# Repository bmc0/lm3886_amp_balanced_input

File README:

A 50W@8Ω balanced-input power amp using the LM3886 chip.

Directories:
  lm3886_amp_balanced_input/    - Amplifier board (one channel)
  lm3886_psu/                   - Power supply (2-channel version)
  lm3886_psu_4ch/               - Power supply (4-channel version)
  lm3886_soft_start_v2/         - Optional soft start

License:
  All works contained in this repository are released under a
  CC BY-SA 4.0 license. Copyright (c) Michael Barbour, 2020.

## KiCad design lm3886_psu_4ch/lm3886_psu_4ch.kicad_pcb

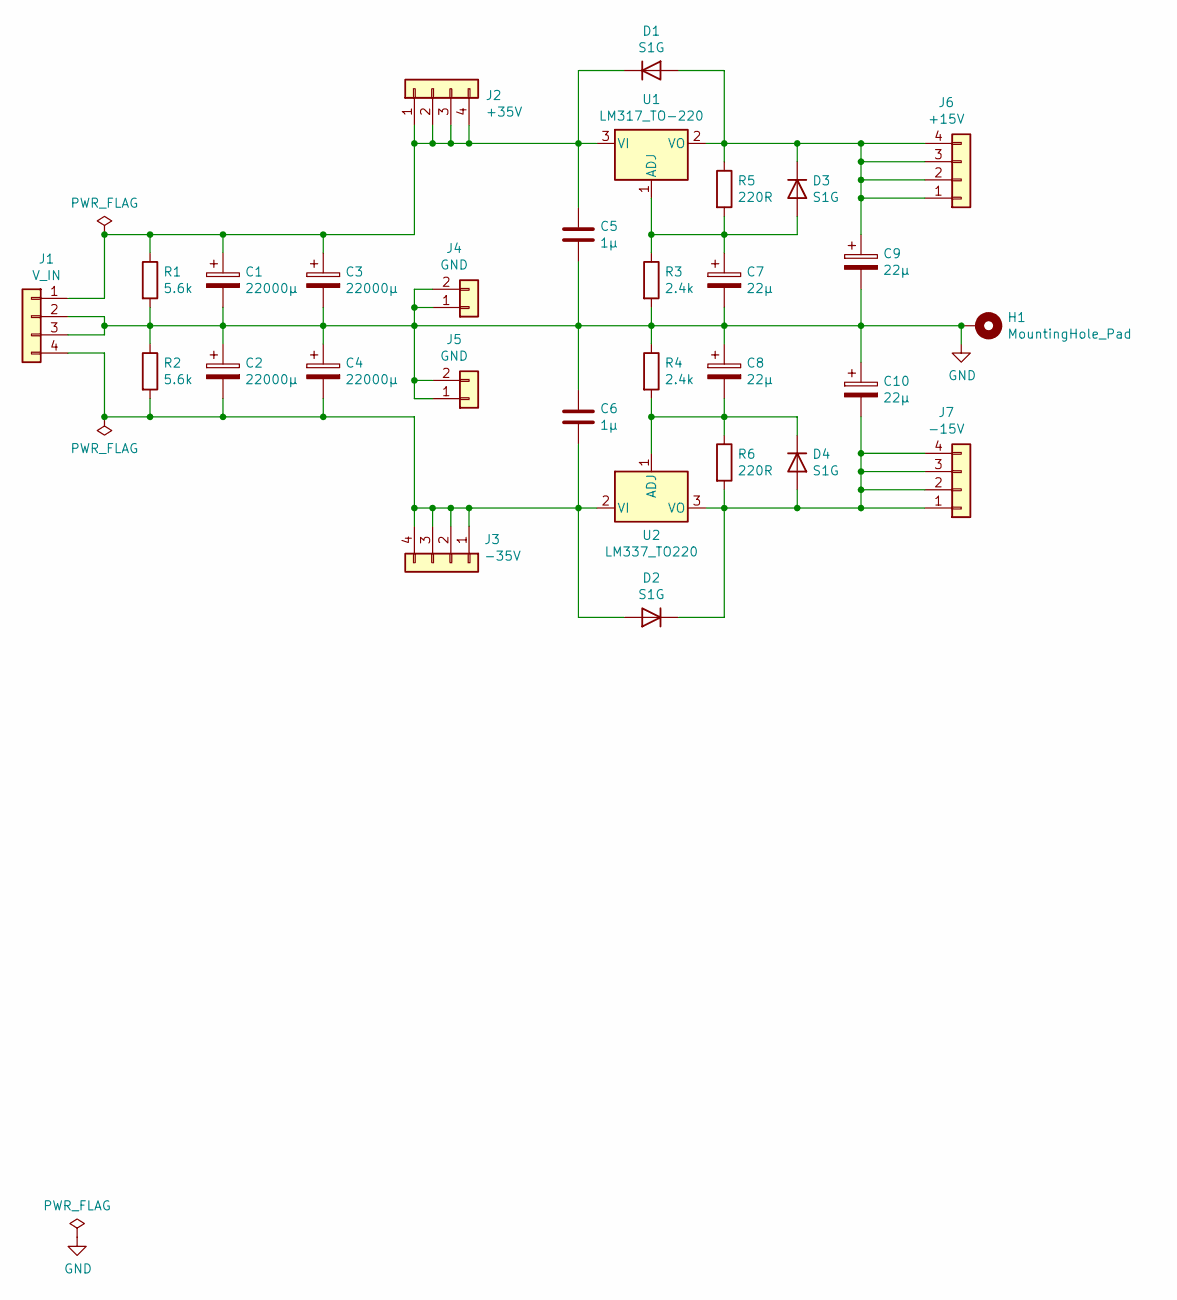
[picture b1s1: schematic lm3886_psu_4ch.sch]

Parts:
C1, C2, C3, C4: 22000µ; CP_Radial_D35.0mm_P10.00mm_SnapIn
C5, C6: 1µ; C_1206_3216Metric
C7, C8, C9, C10: 22µ; CP_Radial_D5.0mm_P2.00mm
D1, D2, D3, D4: S1G; D_SMA
H1: MountingHole_Pad; MountingHole_3.2mm_M3_Pad_Via
J1: V_IN; TerminalBlock_Phoenix_PT-1,5-4-5.0-H_1x04_P5.00mm_Horizontal
J2: +35V; TerminalBlock_Phoenix_PT-1,5-4-5.0-H_1x04_P5.00mm_Horizontal
J3: -35V; TerminalBlock_Phoenix_PT-1,5-4-5.0-H_1x04_P5.00mm_Horizontal
J4, J5: GND; TerminalBlock_Phoenix_PT-1,5-2-5.0-H_1x02_P5.00mm_Horizontal
J6: +15V; TerminalBlock_Phoenix_PT-1,5-4-3.5-H_1x04_P3.50mm_Horizontal
J7: -15V; TerminalBlock_Phoenix_PT-1,5-4-3.5-H_1x04_P3.50mm_Horizontal
R1, R2: 5.6k; R_Axial_DIN0411_L9.9mm_D3.6mm_P15.24mm_Horizontal
R3, R4: 2.4k; R_1206_3216Metric
R5, R6: 220R; R_1206_3216Metric
U1: LM317_TO-220; TO-220-3_Vertical
U2: LM337_TO220; TO-220-3_Vertical

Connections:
GND: C1.2, C2.1, C3.2, C4.1, C5.2, C6.1, C7.2, C8.1, C9.2, C10.1, H1.1, J1.2, J1.3, J4.1, J4.2, J5.1, J5.2, R1.2, R2.1, R3.2, R4.1
unnamed: C1.1, C3.1, C5.1, D1.1 (K), J1.1, J2.1, J2.2, J2.3, J2.4, R1.1, U1.3 (VI)
unnamed: C2.2, C4.2, C6.2, D2.2 (A), J1.4, J3.1, J3.2, J3.3, J3.4, R2.2, U2.2 (VI)
unnamed: C7.1, D3.2 (A), R3.1, R5.2, U1.1 (ADJ)
unnamed: C8.2, D4.1 (K), R4.2, R6.1, U2.1 (ADJ)
unnamed: C9.1, D1.2 (A), D3.1 (K), J6.1, J6.2, J6.3, J6.4, R5.1, U1.2 (VO)
unnamed: C10.2, D2.1 (K), D4.2 (A), J7.1, J7.2, J7.3, J7.4, R6.2, U2.3 (VO)

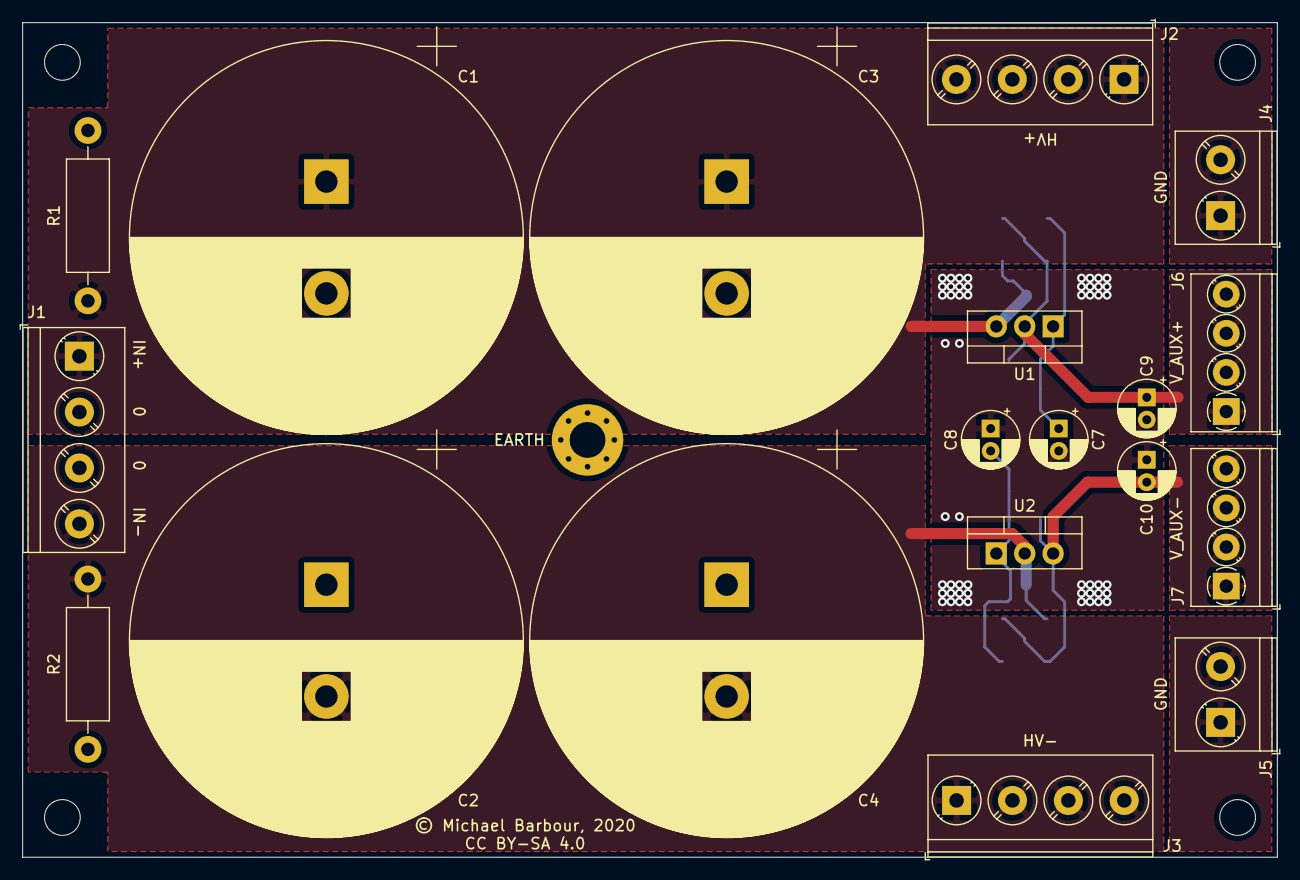
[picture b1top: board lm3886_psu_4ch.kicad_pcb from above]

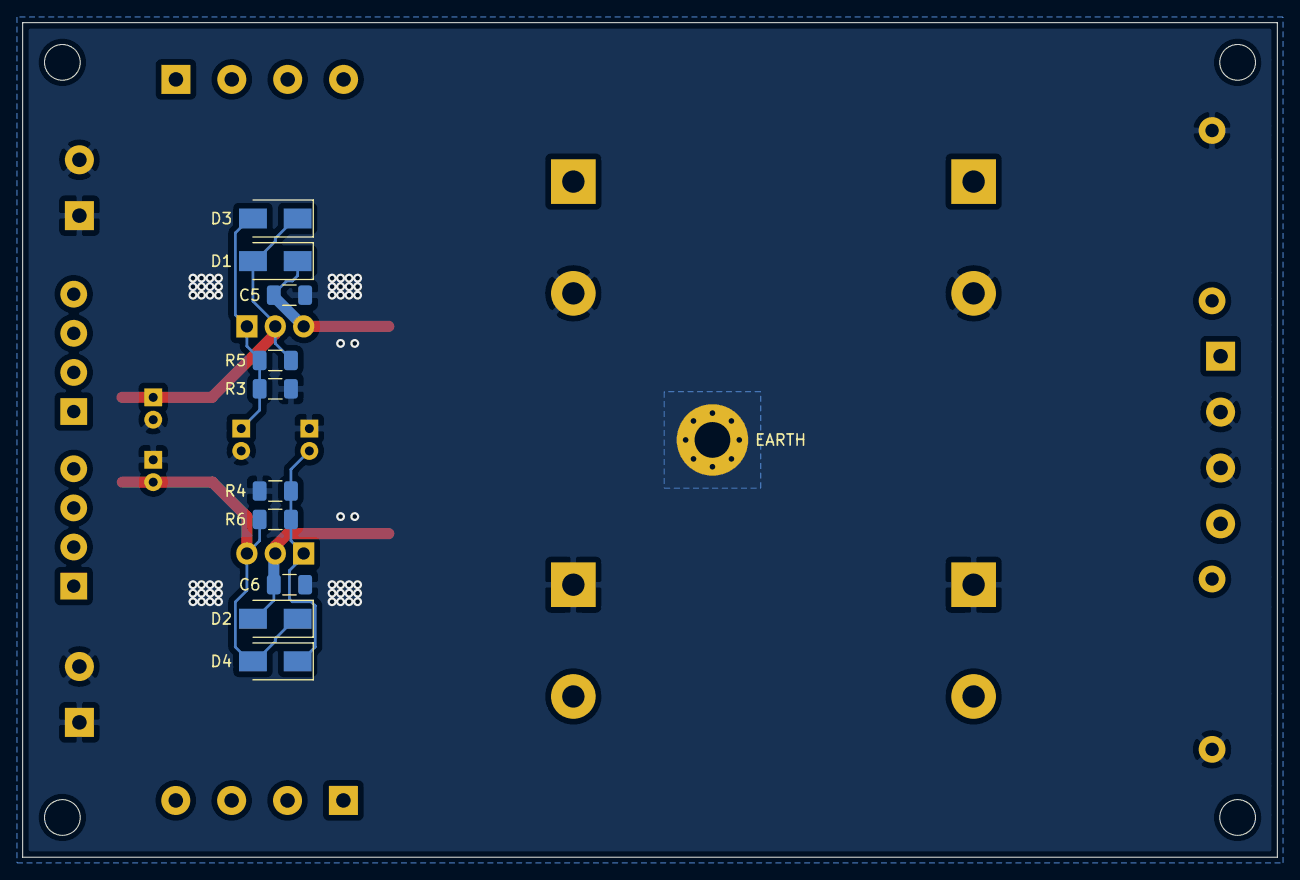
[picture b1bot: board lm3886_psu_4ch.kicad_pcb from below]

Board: 2 copper layers, 112.3 x 74.7 mm, 30 parts (10 on the bottom side), 7 nets.

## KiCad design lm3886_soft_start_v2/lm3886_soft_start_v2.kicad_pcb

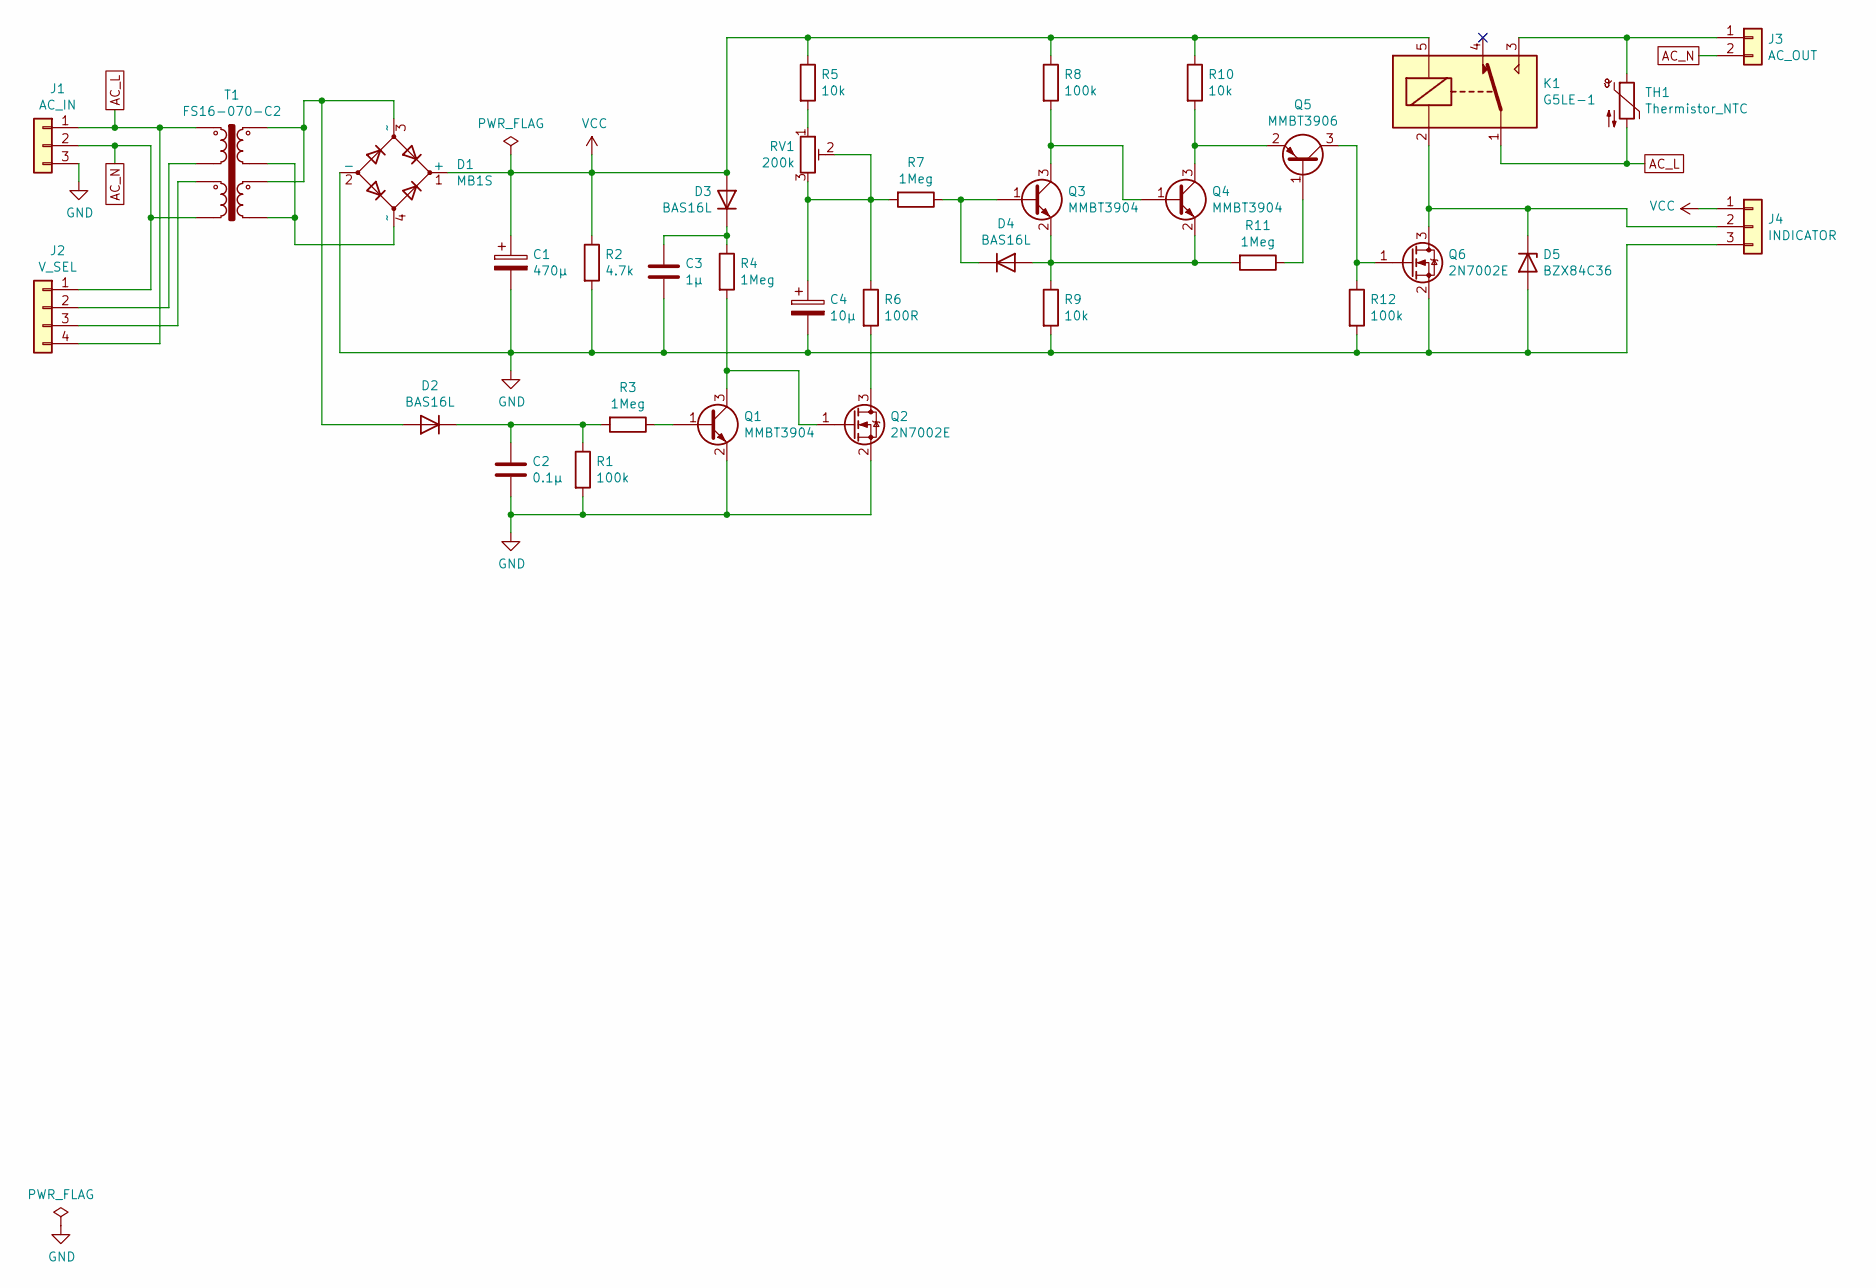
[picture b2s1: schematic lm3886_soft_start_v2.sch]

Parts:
C1: 470µ; CP_Radial_D10.0mm_P5.00mm
C2: 0.1µ; C_0603_1608Metric
C3: 1µ; C_0805_2012Metric
C4: 10µ; CP_Radial_D5.0mm_P2.00mm
D1: MB1S; TO-269AA
D2, D3, D4: BAS16L; D_SOT-23_ANK
D5: BZX84C36; D_SOT-23_ANK
J1: AC_IN; TerminalBlock_Phoenix_PT-1,5-3-5.0-H_1x03_P5.00mm_Horizontal
J2: V_SEL; SolderWire-0.5sqmm_1x04_P4.6mm_D0.9mm_OD2.1mm
J3: AC_OUT; TerminalBlock_Phoenix_PT-1,5-2-5.0-H_1x02_P5.00mm_Horizontal
J4: INDICATOR; PinHeader_1x03_P2.54mm_Vertical
K1: G5LE-1; Relay_SPDT_Omron-G5LE-1
Q1, Q3, Q4: MMBT3904; SOT-23
Q2, Q6: 2N7002E; SOT-23
Q5: MMBT3906; SOT-23
R1, R8, R12: 100k; R_0603_1608Metric
R2: 4.7k; R_1206_3216Metric
R3, R4, R7, R11: 1Meg; R_0603_1608Metric
R5, R9, R10: 10k; R_0603_1608Metric
R6: 100R; R_0603_1608Metric
RV1: 200k; Potentiometer_Nidec_Copal_CT-6EP
T1: FS16-070-C2; Triad_FS16-070-C2
TH1: Thermistor_NTC; NTC_Thermistor_D16mm_P7.5mm

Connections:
AC_L: J1.1, J2.4, K1.1, T1.1, TH1.2
AC_N: J1.2, J2.1, J3.2, T1.4
GND: C1.2, C2.2, C3.2, C4.2, D1.2 (-), D5.2 (A), J1.3, J4.3, Q1.2 (E), Q2.2 (S), Q6.2 (S), R1.2, R2.2, R9.2, R12.2
unnamed: C2.1, D2.1 (K), R1.1, R3.2
unnamed: C3.1, D3.1 (K), R4.1
unnamed: C4.1, R6.1, R7.2, RV1.2, RV1.3
unnamed: D1.3 (~~), D2.2 (A), T1.5, T1.7
unnamed: D1.4 (~~), T1.6, T1.8
unnamed: D4.1 (K), Q3.1 (B), R7.1
unnamed: D4.2 (A), Q3.2 (E), Q4.2 (E), R9.1, R11.2
unnamed: D5.1 (K), J4.2, K1.2, Q6.3 (D)
unnamed: J2.2, T1.2
unnamed: J2.3, T1.3
unnamed: J3.1, K1.3, TH1.1
unnamed: Q1.1 (B), R3.1
unnamed: Q1.3 (C), Q2.1 (G), R4.2
unnamed: Q2.3 (D), R6.2
unnamed: Q3.3 (C), Q4.1 (B), R8.2
unnamed: Q4.3 (C), Q5.2 (E), R10.2
unnamed: Q5.1 (B), R11.1
unnamed: Q5.3 (C), Q6.1 (G), R12.1
unnamed: R5.2, RV1.1
VCC: C1.1, D1.1 (+), D3.2 (A), J4.1, K1.5, R2.1, R5.1, R8.1, R10.1

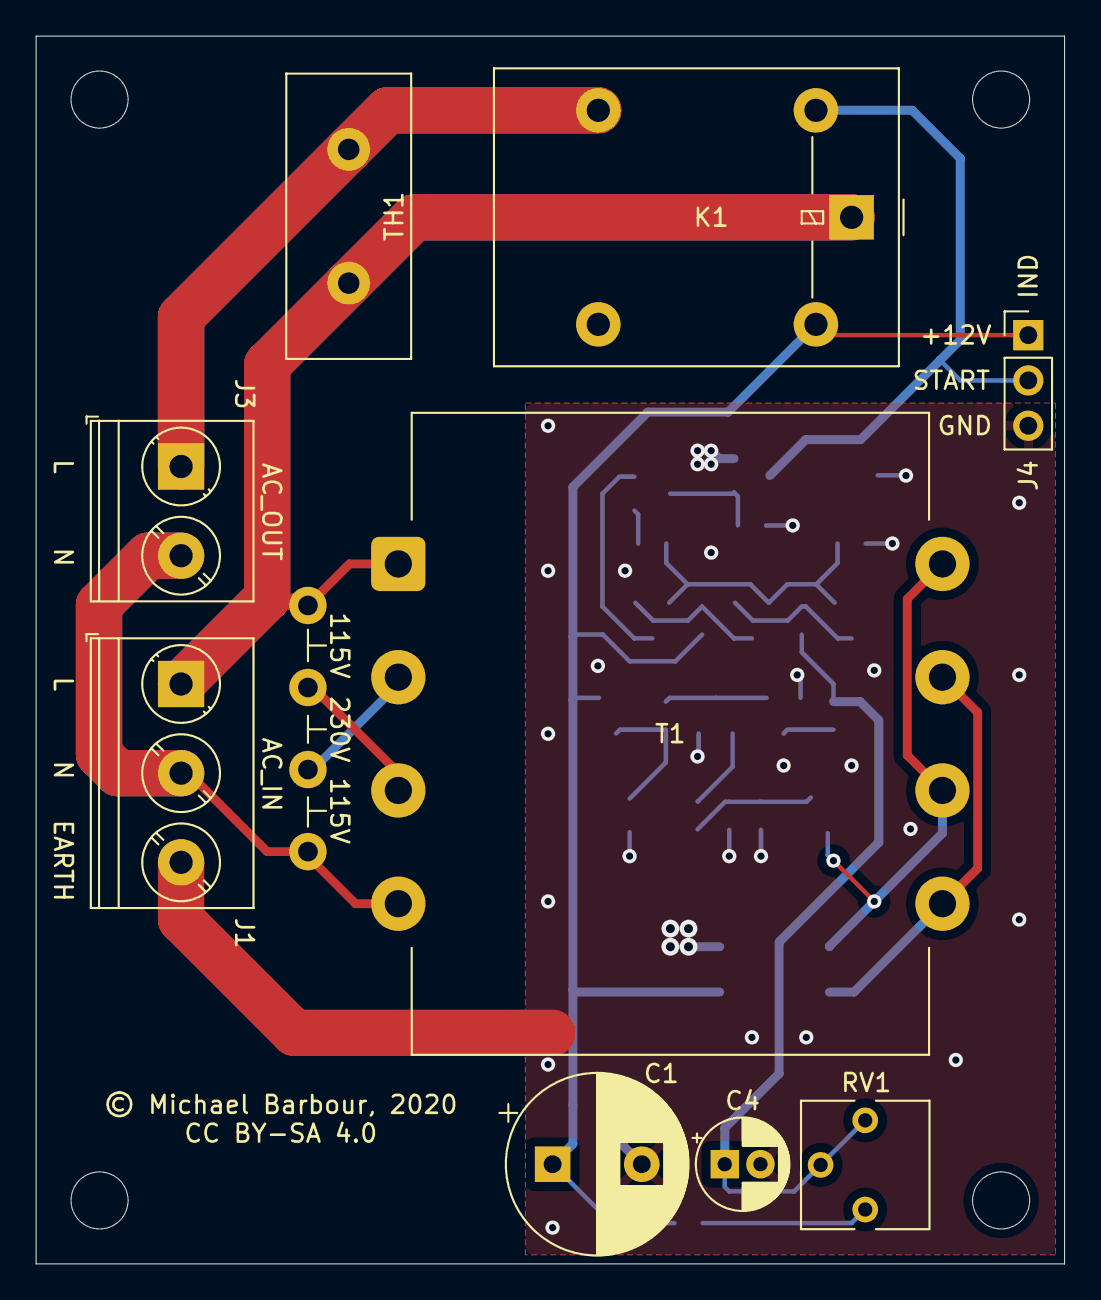
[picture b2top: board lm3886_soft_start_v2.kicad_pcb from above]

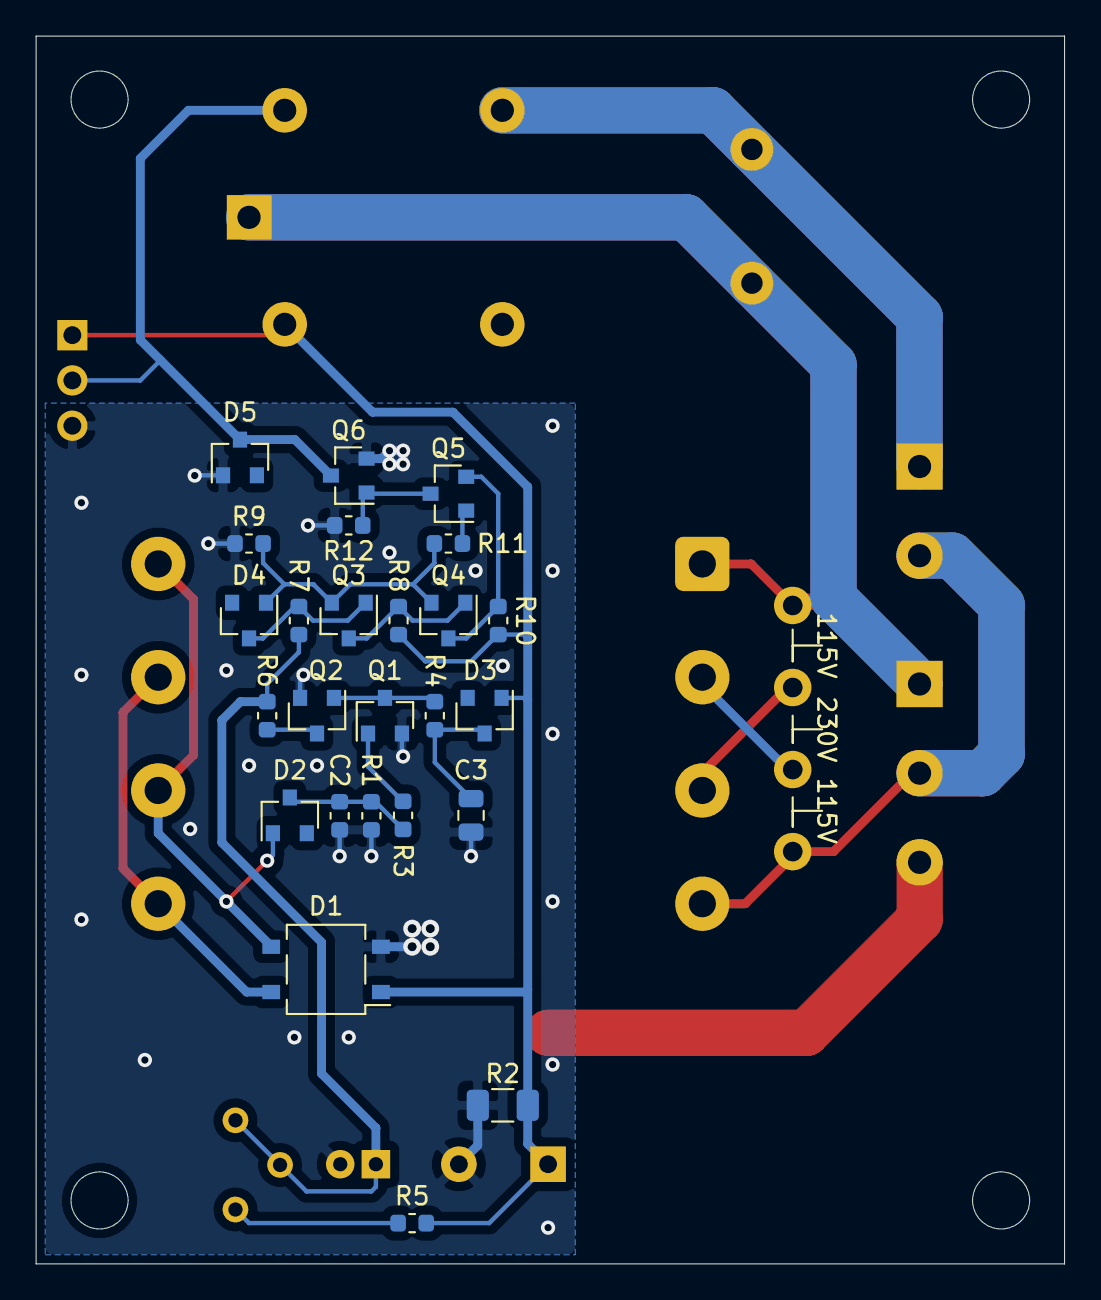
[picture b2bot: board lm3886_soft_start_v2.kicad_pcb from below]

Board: 2 copper layers, 57.7 x 68.8 mm, 35 parts (25 on the bottom side), 23 nets.

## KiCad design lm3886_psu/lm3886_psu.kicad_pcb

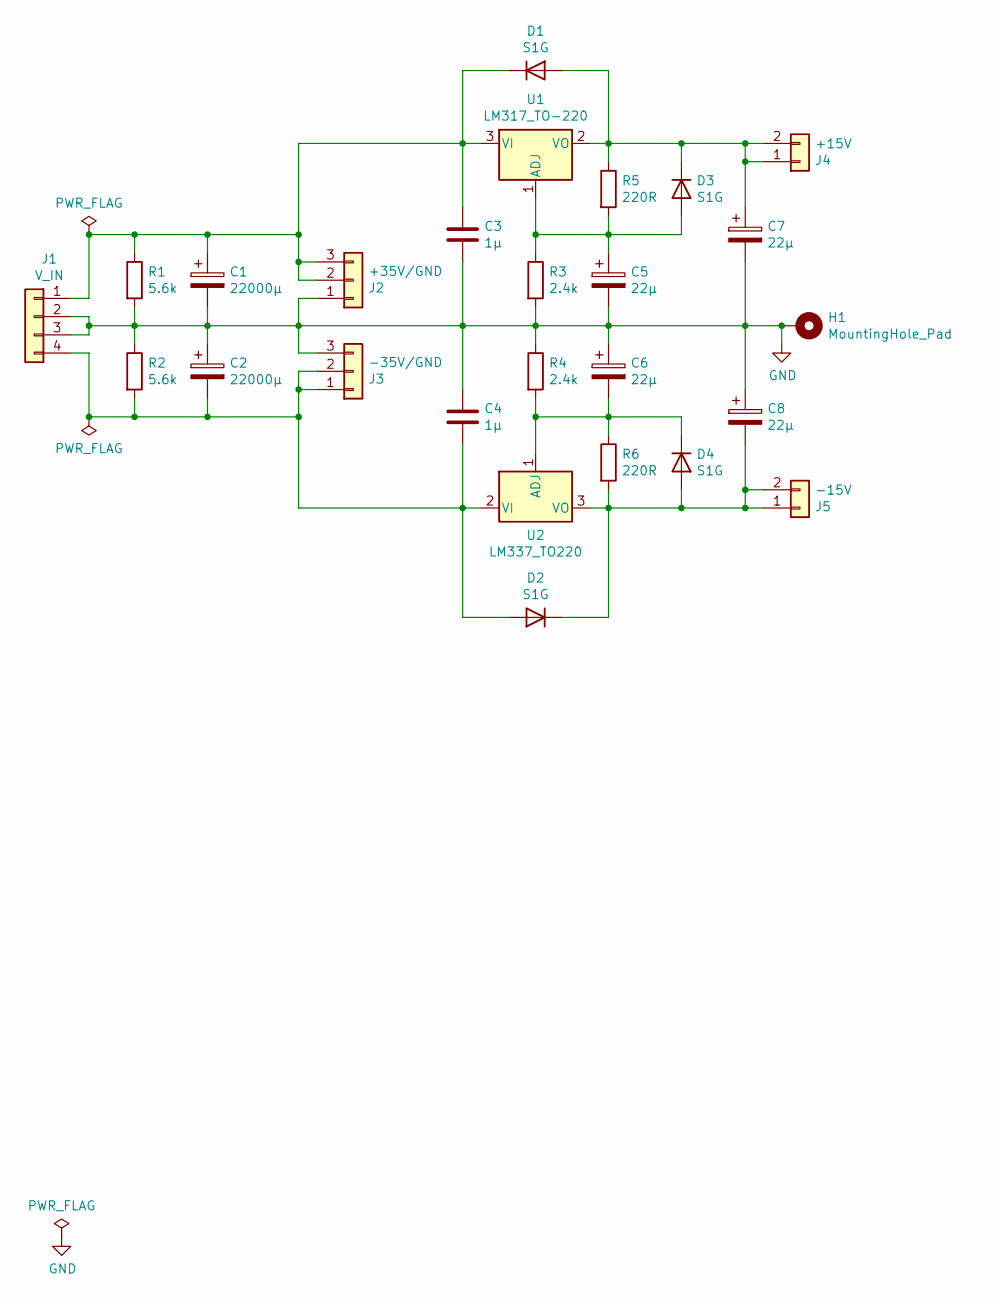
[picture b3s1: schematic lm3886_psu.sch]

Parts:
C1, C2: 22000µ; CP_Radial_D35.0mm_P10.00mm_SnapIn
C3, C4: 1µ; C_1206_3216Metric
C5, C6, C7, C8: 22µ; CP_Radial_D5.0mm_P2.00mm
D1, D2, D3, D4: S1G; D_SMA
H1: MountingHole_Pad; MountingHole_3.2mm_M3_Pad_Via
J1: V_IN; TerminalBlock_Phoenix_PT-1,5-4-5.0-H_1x04_P5.00mm_Horizontal
J2: +35V/GND; TerminalBlock_Phoenix_PT-1,5-3-5.0-H_1x03_P5.00mm_Horizontal
J3: -35V/GND; TerminalBlock_Phoenix_PT-1,5-3-5.0-H_1x03_P5.00mm_Horizontal
J4: +15V; TerminalBlock_Phoenix_PT-1,5-2-3.5-H_1x02_P3.50mm_Horizontal
J5: -15V; TerminalBlock_Phoenix_PT-1,5-2-3.5-H_1x02_P3.50mm_Horizontal
R1, R2: 5.6k; R_Axial_DIN0411_L9.9mm_D3.6mm_P15.24mm_Horizontal
R3, R4: 2.4k; R_1206_3216Metric
R5, R6: 220R; R_1206_3216Metric
U1: LM317_TO-220; TO-220-3_Vertical
U2: LM337_TO220; TO-220-3_Vertical

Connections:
GND: C1.2, C2.1, C3.2, C4.1, C5.2, C6.1, C7.2, C8.1, H1.1, J1.2, J1.3, J2.1, J3.3, R1.2, R2.1, R3.2, R4.1
unnamed: C1.1, C3.1, D1.1 (K), J1.1, J2.2, J2.3, R1.1, U1.3 (VI)
unnamed: C2.2, C4.2, D2.2 (A), J1.4, J3.1, J3.2, R2.2, U2.2 (VI)
unnamed: C5.1, D3.2 (A), R3.1, R5.2, U1.1 (ADJ)
unnamed: C6.2, D4.1 (K), R4.2, R6.1, U2.1 (ADJ)
unnamed: C7.1, D1.2 (A), D3.1 (K), J4.1, J4.2, R5.1, U1.2 (VO)
unnamed: C8.2, D2.1 (K), D4.2 (A), J5.1, J5.2, R6.2, U2.3 (VO)

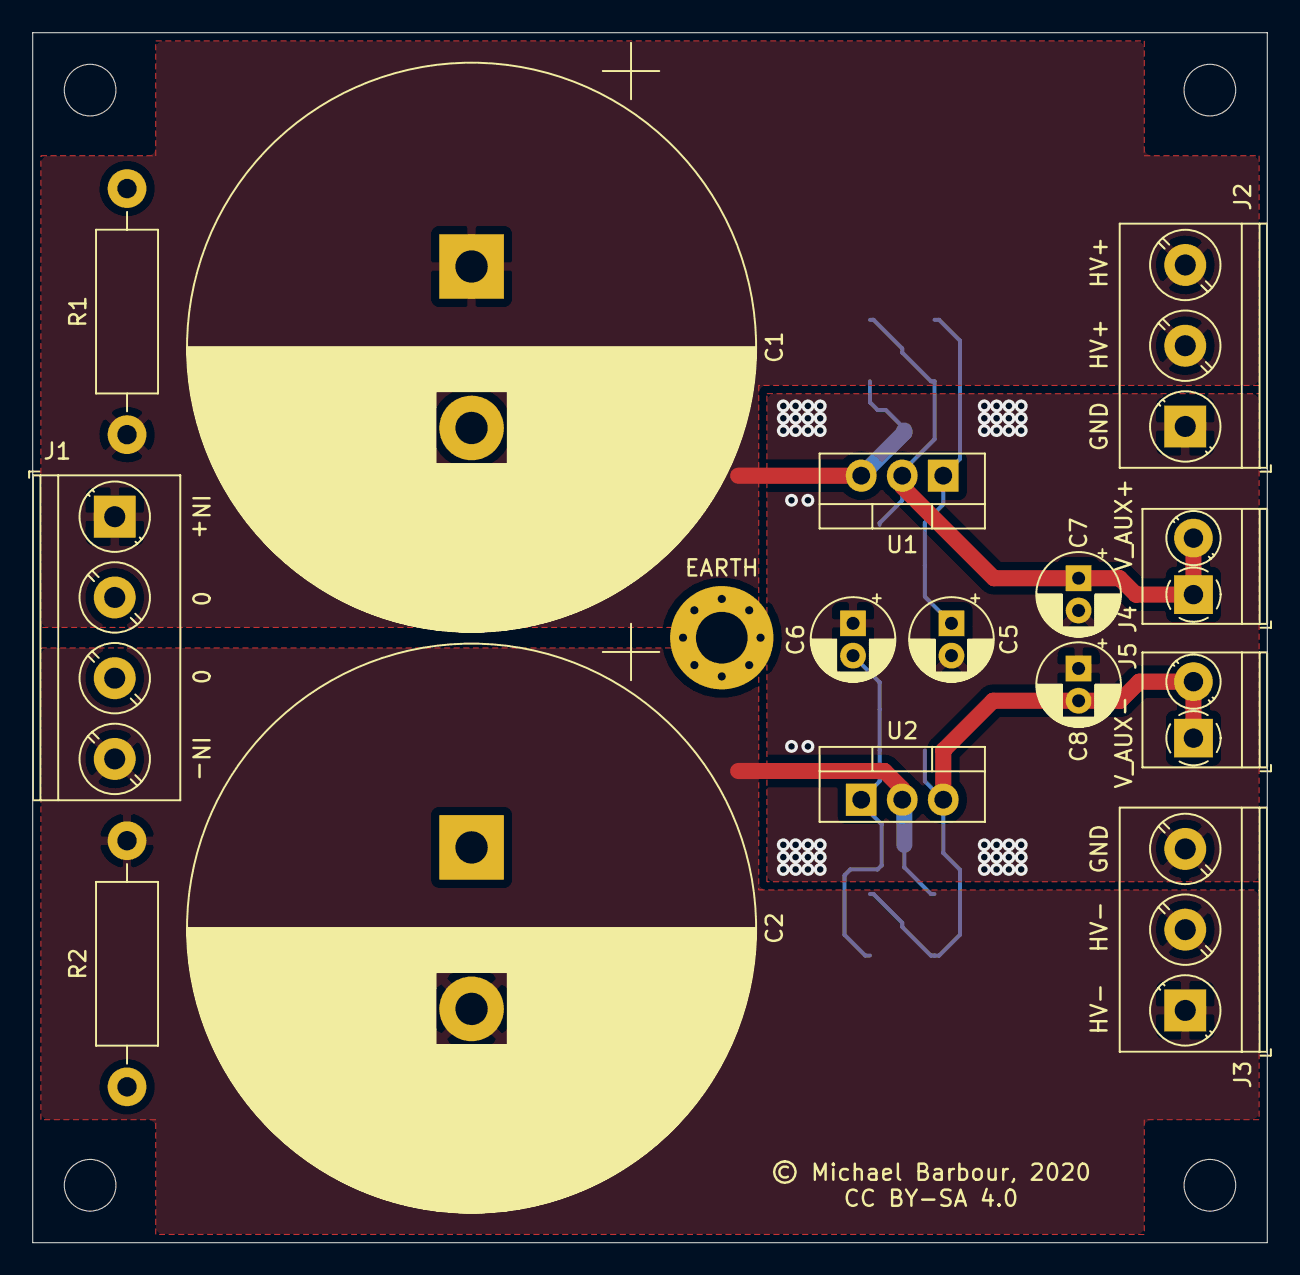
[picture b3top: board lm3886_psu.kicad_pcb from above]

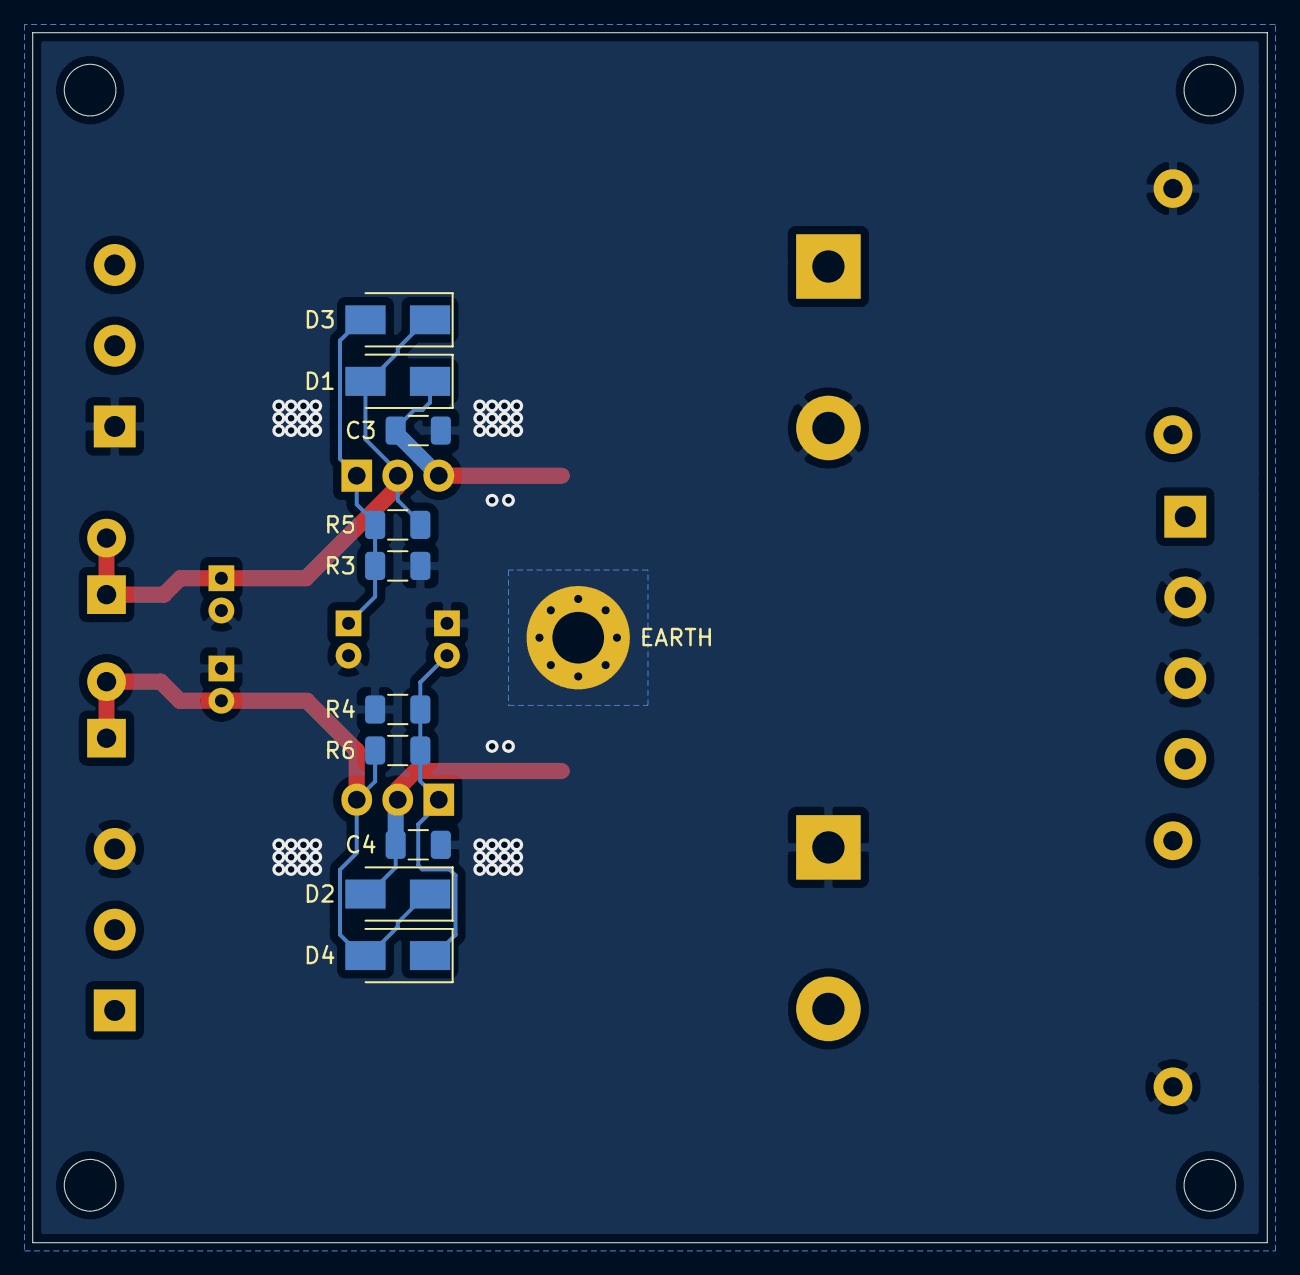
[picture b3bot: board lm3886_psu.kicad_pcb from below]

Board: 2 copper layers, 76.5 x 74.9 mm, 26 parts (10 on the bottom side), 7 nets.

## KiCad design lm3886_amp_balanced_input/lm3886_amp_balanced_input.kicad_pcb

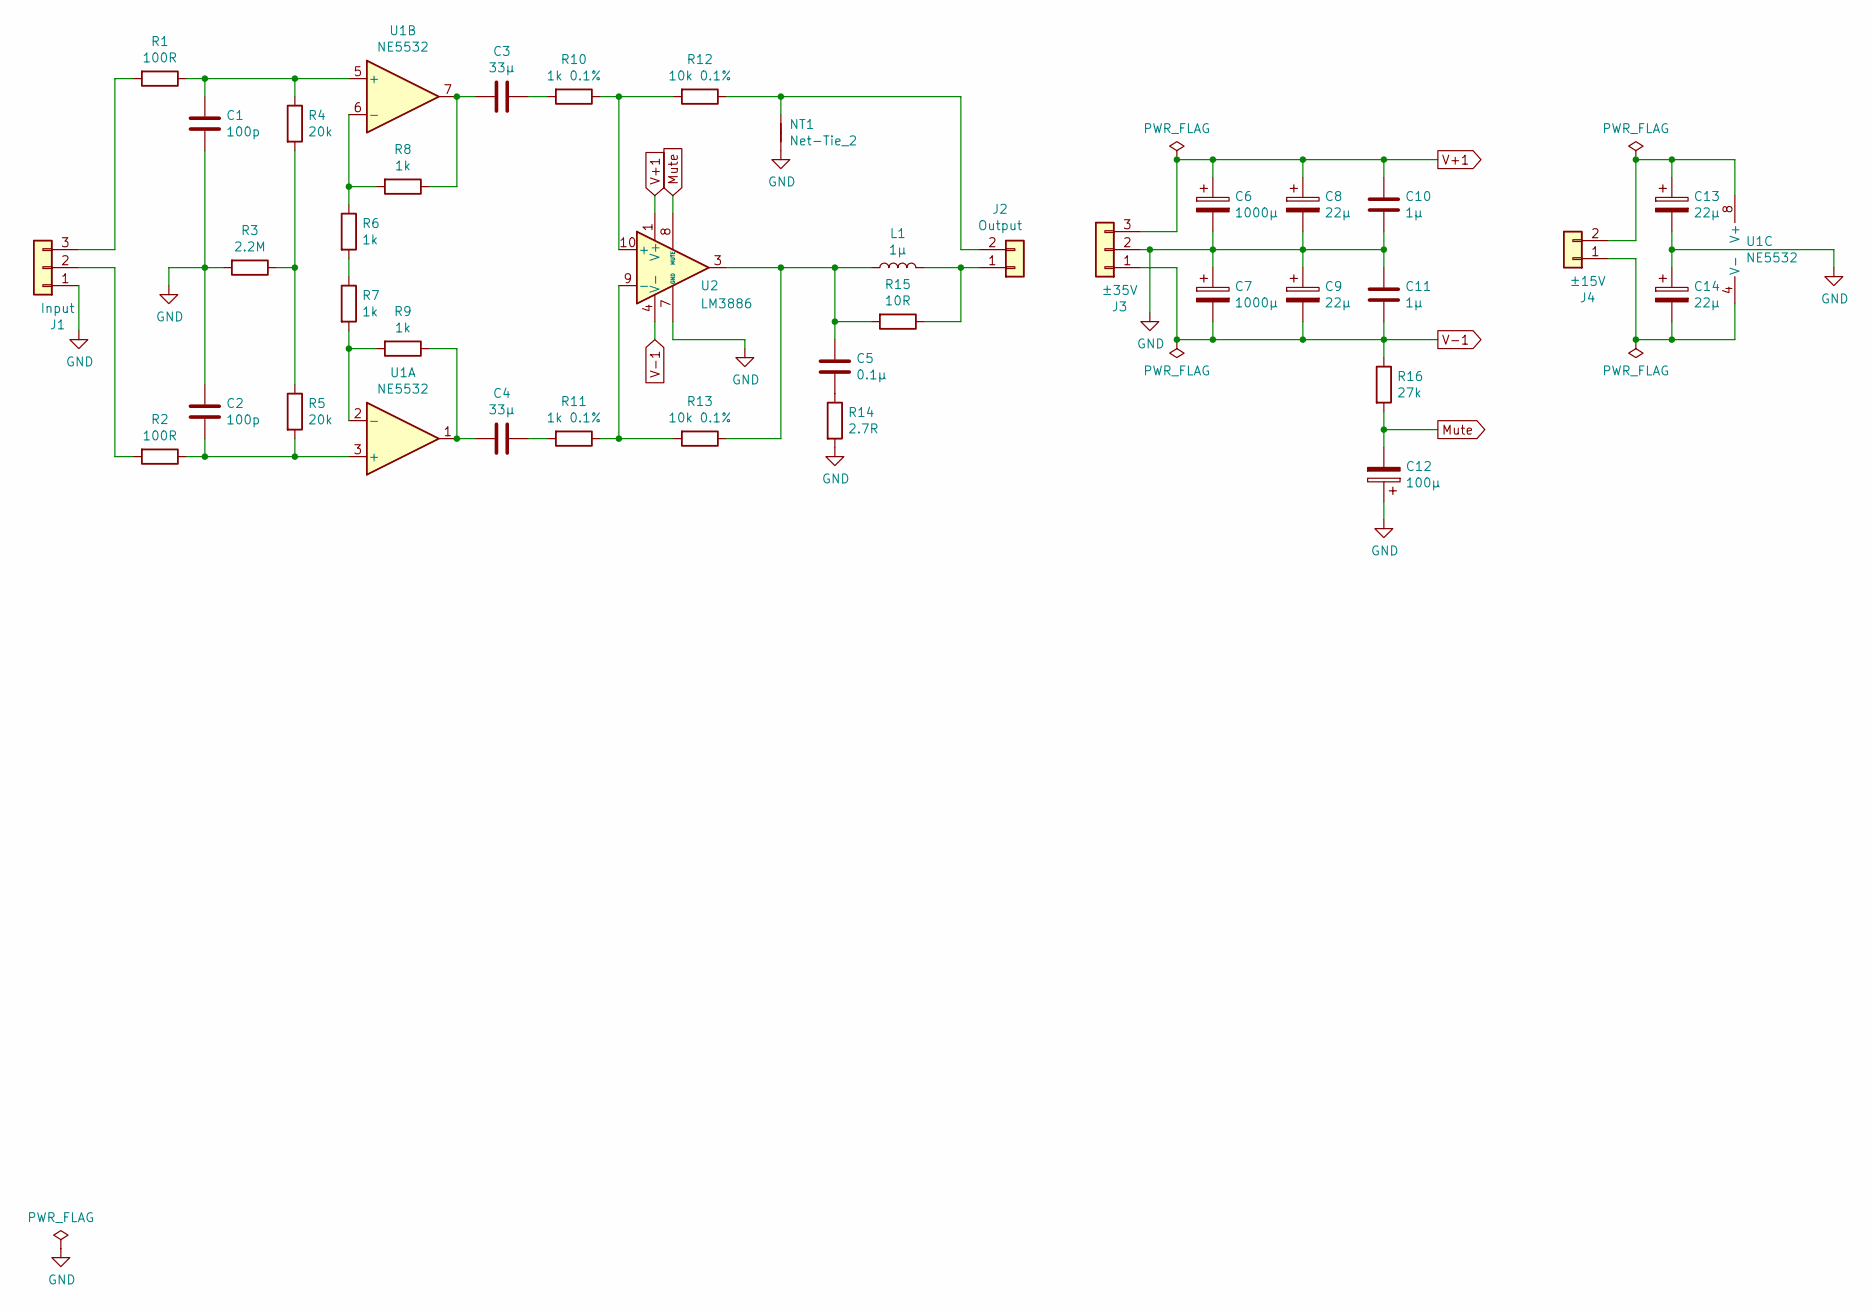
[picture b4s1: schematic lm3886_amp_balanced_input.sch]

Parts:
C1, C2: 100p; C_0603_1608Metric
C3, C4: 33µ; C_Radial_D6.3mm_H11.0mm_P2.50mm
C5: 0.1µ; C_Rect_L7.2mm_W2.5mm_P5.00mm_FKS2_FKP2_MKS2_MKP2
C6, C7: 1000µ; CP_Radial_D16.0mm_P7.50mm
C8, C9, C13, C14: 22µ; CP_Radial_D5.0mm_P2.00mm
C10, C11: 1µ; C_1206_3216Metric
C12: 100µ; CP_Radial_D5.0mm_P2.00mm
J1: Input; TerminalBlock_Phoenix_PT-1,5-3-3.5-H_1x03_P3.50mm_Horizontal
J2: Output; TerminalBlock_Phoenix_PT-1,5-2-5.0-H_1x02_P5.00mm_Horizontal
J3: ±35V; TerminalBlock_Phoenix_PT-1,5-3-5.0-H_1x03_P5.00mm_Horizontal
J4: ±15V; TerminalBlock_Phoenix_PT-1,5-2-3.5-H_1x02_P3.50mm_Horizontal
L1: 1µ; lm3886_output_inductor_1µH
NT1: Net-Tie_2; NetTie-2_SMD_Pad2.0mm
R1, R2: 100R; R_0603_1608Metric
R3: 2.2M; R_0603_1608Metric
R4, R5: 20k; R_0603_1608Metric
R6, R7, R8, R9: 1k; R_0603_1608Metric
R10, R11: 1k 0.1%; R_0805_2012Metric
R12, R13: 10k 0.1%; R_0805_2012Metric
R14: 2.7R; R_Axial_DIN0411_L9.9mm_D3.6mm_P12.70mm_Horizontal
R15: 10R; R_Axial_DIN0411_L9.9mm_D3.6mm_P12.70mm_Horizontal
R16: 27k; R_0805_2012Metric
U1: NE5532; SOIC-8_3.9x4.9mm_P1.27mm
U2: LM3886; TO-220-11_P3.4x5.08mm_StaggerOdd_Lead4.85mm_Vertical_LM3886

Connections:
GND: C1.2, C2.1, C6.2, C7.1, C8.2, C9.1, C10.2, C11.1, C12.1, C13.2, C14.1, J1.1, J3.2, NT1.2, R3.2, R14.2, U2.7 (GND)
Mute: C12.2, R16.2, U2.8 (MUTE)
unnamed: C1.1, R1.1, R4.1, U1.5 (+)
unnamed: C2.2, R2.1, R5.2, U1.3 (+)
unnamed: C3.1, R10.2
unnamed: C3.2, R8.1, U1.7
unnamed: C4.1, R11.2
unnamed: C4.2, R9.1, U1.1
unnamed: C5.1, L1.1, R13.1, R15.2, U2.3
unnamed: C5.2, R14.1
unnamed: C13.1, J4.2, U1.8 (V+)
unnamed: C14.2, J4.1, U1.4 (V-)
unnamed: J1.2, R2.2
unnamed: J1.3, R1.2
unnamed: J2.1, L1.2, R15.1
unnamed: J2.2, NT1.1, R12.1
unnamed: R3.1, R4.2, R5.1
unnamed: R6.1, R8.2, U1.6 (-)
unnamed: R6.2, R7.1
unnamed: R7.2, R9.2, U1.2 (-)
unnamed: R10.1, R12.2, U2.10 (+)
unnamed: R11.1, R13.2, U2.9 (-)
V+1: C6.1, C8.1, C10.1, J3.3, U2.1 (V+), U2.5 (V+)
V-1: C7.2, C9.2, C11.2, J3.1, R16.1, U2.4 (V-)

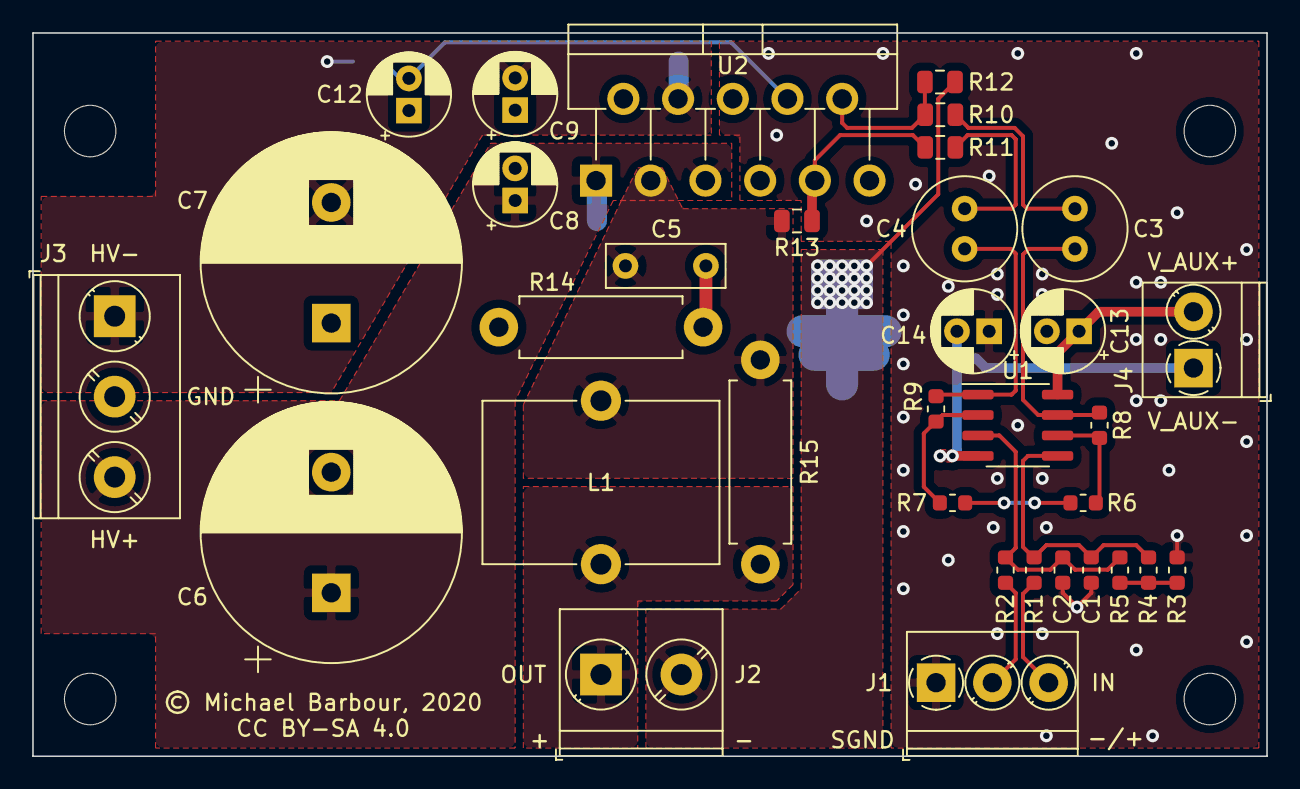
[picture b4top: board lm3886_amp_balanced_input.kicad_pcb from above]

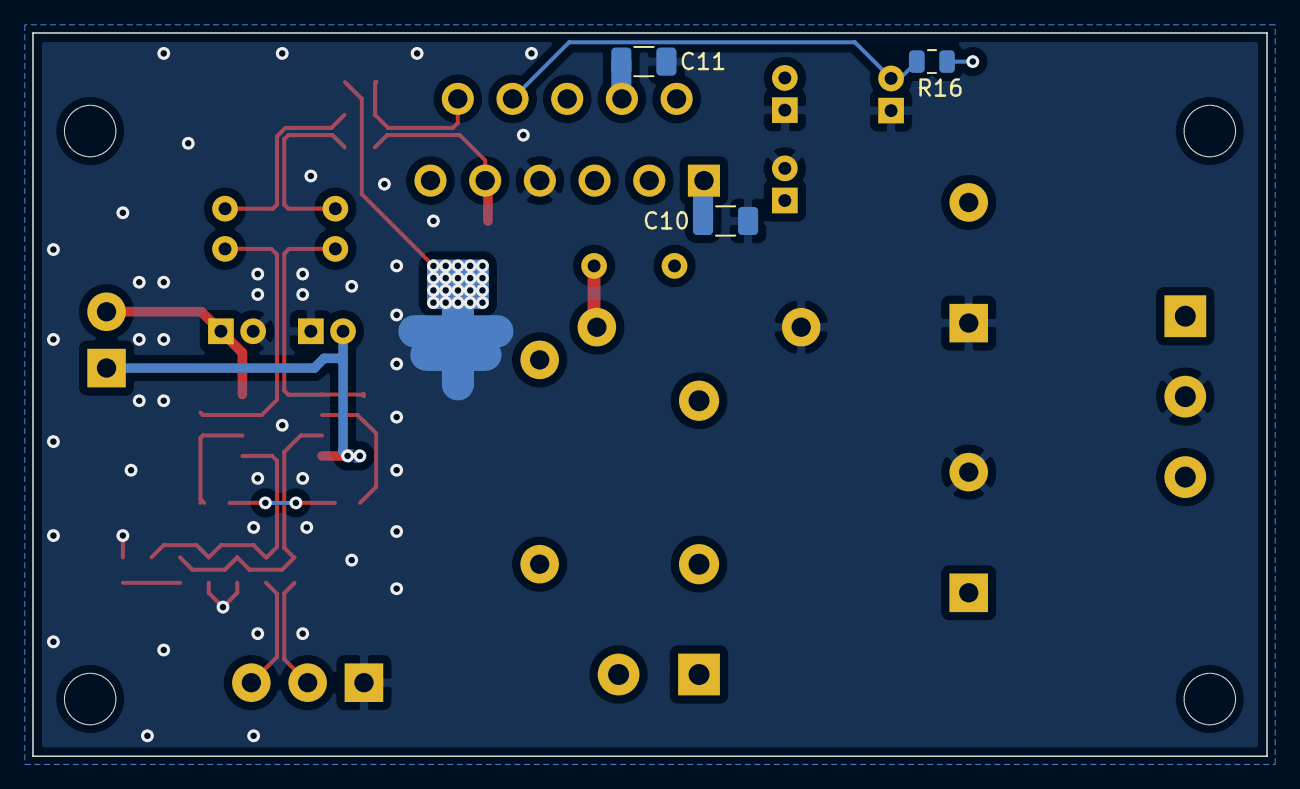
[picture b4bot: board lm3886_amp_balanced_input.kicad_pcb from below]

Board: 2 copper layers, 76.7 x 45.0 mm, 38 parts (4 on the bottom side), 24 nets.

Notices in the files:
lm3886_amp_balanced_input/lm3886_amp_balanced_input.kicad_pcb:
© Michael Barbour, 2020
CC BY-SA 4.0
